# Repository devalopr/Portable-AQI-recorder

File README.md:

# Portable AQI Recorder — V3 (custom PCB)

A handheld air-quality recorder on a custom main board: an ESP32-C3-MINI-1 module reads a Sensirion SEN5x or SEN6x particulate sensor and an optional SCD4x CO₂ sensor (SCD40, SCD41 or SCD43), shows readings on a 2.4" ST7789 TFT with three buttons, and has Wi-Fi and BLE on the module.

This branch holds the **V3 main PCB only**. Everything else lives elsewhere:

| What | Where |
|---|---|
| ESP32-C3 Super Mini build without a PCB: firmware, Web Bluetooth app, wiring | [V2 branch](https://github.com/devalopr/Portable-AQI-recorder/tree/V2) |
| 18650 battery board (IP5310, USB-C in/out, battery % over PWM) | Separate product: [18650-USB-C-UPS](https://github.com/devalopr/18650-USB-C-UPS) (private) |
| Rev A boards and earlier design history | Git history of this branch (commit `34dd5cf`) |

## Main board (Rev B)

**[hardware/rev-b/main](hardware/rev-b/main/README.md)** — KiCad 10 project, 47 × 76 mm, two layers, fully routed. Start with its README: layout, pin map, connectors, cost, checks and open items before fabrication.

- **Display:** 2.4" 240 × 320 ST7789 TFT on the front, with the three buttons below it. An e-paper display can be fitted instead through an external adapter on J6.
- **Sensors:** SEN5x and SEN6x connectors (fit one PM module) and a CO₂ island for an optional SCD40, SCD41 or SCD43, soldered by hand later. Everything else on the board comes assembled; only the CO₂ sensor and the J6/J8 headers are left unfitted.
- **Power and data:** USB-C J1 is the only input. It takes 5 V and USB data from the battery board's USB-C output, or straight from a charger or computer. Battery % arrives as PWM on J2.
- **Cost:** about $4.63 per board at 1000 (parts, 2-layer fabrication and JLC assembly); see [review/COST.md](hardware/rev-b/main/review/COST.md).

## Repository layout

| Path | Contents |
|---|---|
| [firmware](firmware/README.md) | Main board firmware (PlatformIO). |
| [hardware/rev-b/main](hardware/rev-b/main/README.md) | Schematic, PCB, libraries and 3D models; `review/` has the BOM, placement file, PDF, renders, DRC/ERC reports and routing files. |
| [hardware/rev-b/scripts](hardware/rev-b/scripts) | Python/shell pipeline that generates the schematic and places, routes and checks the board (see "Regenerating" in the main README). |
| [hardware/rev-b/firmware/telemetry](hardware/rev-b/firmware/telemetry/README.md) | ESP32 receiver for the battery board's battery-% PWM signal. |
| [hardware/rev-b/references](hardware/rev-b/references) | Datasheets for parts on this board. |
| [hardware/design-brief.md](hardware/design-brief.md) | The original product brief the boards were designed from. |

## Firmware

**[firmware/](firmware/README.md)** — PlatformIO/Arduino firmware for this board, ported from the V2 firmware: auto-detects SEN5x or SEN6x and any SCD4x, shows AQI and the other readings on the TFT, records to RAM, streams over BLE (compatible with the V2 web app) and shows the battery % from the battery board. It builds but hasn't run on a built board yet.

The board is programmed and logs over its USB-C port (the ESP32-C3's native USB): switch the board on and run `pio run -t upload` in `firmware/`. If it stops appearing, hold OK while switching it on to force the bootloader.

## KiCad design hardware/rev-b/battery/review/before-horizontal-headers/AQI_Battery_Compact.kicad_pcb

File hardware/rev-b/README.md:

**Current boards (2026-09-27):** main board [main/](main/README.md) (USB-C input + Dupont battery-PWM header) and the battery board, now its own product in the private [18650-USB-C-UPS](https://github.com/devalopr/18650-USB-C-UPS) repo. The sections below describe earlier battery-board revisions.

# Compact standalone 18650 supply — Rev B engineering review

## Current BOM handoff — 2026-09-11

For continuing cost-reduction work, use [cost-revision/review/engineering-bom.csv](cost-revision/review/engineering-bom.csv) and [the sourcing handoff](cost-revision/BOM-HANDOFF.md). Procurement metadata is synchronized into the cost-revision schematic and design.json. The older battery/review CSV and the routed-board description below describe an earlier circuit.

The generic holder is costed at INR30 based on the user's under-INR30 source. The current priced subset including that allowance is INR261.21 per board at 1,000 boards; unresolved parts and manufacturing remain additional. This is not a complete production quotation.

Open **battery/AQI_Battery_Compact.kicad_pro**. This is the routed electrical revision; the older `AQI_Battery_Compact_Mechanical` file is only the superseded fit study. Rev A is unchanged.

## Size and interfaces

- **26.2 × 88 mm, two copper layers, 1.6 mm board.** Approximately 5.55 mm wider overall than the 20.65 mm holder model. Area is about 42% smaller than the old 44 × 90 mm board.
- Keystone **1042** surface-mount holder for a standard 65 mm cell, with its actual KiCad STEP model. Terminal pad span limits length; the input connector mounting geometry required the extra 0.5 mm over the initial fit study.
- Bottom input: Amphenol **12401610E4#2A**, centred on the board, with surface-mount signal contacts and through-hole shell anchors. Input USB data are passed to the optional GH interface.
- Top output: GCT **USB4135-GF-A**, power-only, all surface mount. TUSB320 attachment detection and TPS2552 switched/current-limited VBUS are included.
- J8/J9: unpopulated 2.54 mm through-hole rows on both sides of the output USB-C, each carrying 3.3 V, 5 V and GND (pins 1–3). Trim soldered wire ends flush on the holder side. Design load targets are 0.5 A at 5 V and 0.3 A at 3.3 V; USB and auxiliary loads share the converter budget. These are not bench-qualified ratings.
- JST GH host connector and MAX17048 fuel gauge retained for AQI compatibility. Neither is required to select charging current or operate the standalone indicator. R18/R19 I2C pullups are intentionally unpopulated when a host supplies pullups.

## Charge-rate selector

Recessed **C&K PCM13SMTR** three-position slide switch. Nominal labels: **500 mA / 1 A / 1.5 A**. Select with input power disconnected. The enclosure should expose a small tool-access opening; the PCB alone cannot enforce tweezers-only access.

BQ25606 switching charger; no MCU, firmware or ESP32 required. VSET is intentionally floating for nominal 4.208 V regulation. R36 (10 kΩ) provides a fixed normal-temperature bypass by default, so no thermistor is required. Optional TH1 is a Vishay NTCS0603E3103FLT 0603 SMD NTC (10 kΩ, B3435). Remove R36 when fitting TH1; never populate both. TH1 measures PCB temperature and does not provide direct cell-temperature monitoring.

R3 = 1.37 kΩ sets the low rate. R4 and R5 = 681 Ω form a tapped resistor ladder selected to ground by switch common pin 3. Calculated nominal rates are approximately **494 / 991 / 1488 mA**. An open selector contact falls back to low; overlapping adjacent contacts cannot add independent parallel branches beyond the high setting. Charger and resistor tolerances still apply.

For a nominal 0.5C target, 1 A corresponds to a 2000 mAh cell and 1.5 A to a 3000 mAh cell. Select within the actual cell manufacturer's charging limit. Cell size does not establish safe charge current. Full charging includes a taper phase and takes longer than two hours at 0.5C.

The input CC controller raises the input limit from nominal 0.50 A to about 1.42 A only when the source advertises at least 1.5 A. Charge current may be reduced by input power, concurrent loads or temperature. Legacy USB host enumeration/current-policy compliance remains a qualification item; this is not a certified universal USB product.

## RGB indicator

One small RGB LED, with 10 kΩ series resistors for dim operation. Autonomous comparator-based battery voltage bands: red below approximately 3.50 V; red + green between approximately 3.50 and 3.91 V; green above approximately 3.91 V. Blue is added during charging and follows the charger fault blink signal. Colours therefore blend while charging. This is an approximate voltage indication, **not a percentage gauge**. The optional MAX17048 supplies percentage data to an external I2C host.

## Validation and limits

- See `battery/review/erc.json`, `drc.json`, `connectivity.json` and `validation.json` for current results.
- All 273 intended electrical pins agree between the schematic netlist and PCB. ERC passes, routing has zero unconnected items and schematic parity passes.
- The dense charger escape includes approximately 2.8 mm total of 0.15 mm battery-net neck-downs; most of the repaired route uses 0.5 mm copper. Verify worst-case charging/discharging temperature rise and voltage drop before production.
- Ten unsuppressed mechanical DRC findings concern opposite-side holder courtyard overlap: four bare-header holes, two input shell anchors, two input locating holes and two selector locating holes. Bare holes are intentionally unpopulated; trim any wires flush. Verify input anchor/peg protrusion and holder clearance with actual parts before fabrication. These findings are not an electrical clearance waiver.
- The STEP includes the actual holder and library component models. RGB, TUSB320 and MAX17048 use explicitly named simplified body/fit models where installed library models were missing. They are not manufacturer-certified detailed CAD.
- Remaining release work: mechanical clearance sign-off, charge/boost thermal and load testing, USB attachment/current-limit behaviour, protection testing, optional temperature-sensing verification, and final exact passive BOM/availability review. Do not order production boards from this engineering package.

## Files

- `battery/AQI_Battery_Compact.kicad_pro`: editable KiCad project.
- `battery/review/AQI_Battery_Compact-fit-check.step`: Fusion fit-check assembly; use Upload/Open in Fusion, then compare to the enclosure.
- `battery/review/compact-holder.png` and `compact-rear.png`: review images.
- `battery/review/engineering-bom.csv`: engineering component list; unresolved passive selections are marked.

The scripts capture intermediate generation and repair operations. The checked-in PCB is the current routed source of truth; do not run the initial generator over it to update a small detail. Back up the working project before regeneration.

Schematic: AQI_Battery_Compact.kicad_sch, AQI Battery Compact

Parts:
C1: 1uF 16V; C_0603_1608Metric
C2: 10uF 16V; C_0805_2012Metric
C3, C4, C17, C19: 22uF 16V; C_0805_2012Metric
C5, C12: 100nF 16V X7R; C_0603_1608Metric; MPN TBD
C6: 4.7uF 10V; C_0603_1608Metric
C7, C11: 10uF 16V X7R; C_0805_2012Metric; MPN TBD
C8, C9, C10, C13, C14: 22uF 16V X7R; C_0805_2012Metric; MPN TBD
C15, C18, C20, C21, C22, C23: 100nF 16V; C_0603_1608Metric
C16: 47nF 16V; C_0603_1608Metric
C24: 100nF 16V X7R; C_0603_1608Metric
D1: Dim RGB; LED_RGB_Lumex_SML-LXT0805SIUGUBW; MPN SML-LXT0805SIUGUBW
D2: USBLC6-2SC6; SOT-23-6; MPN USBLC6-2SC6
J1: USB-C INPUT + DATA; USB_C_Receptacle_Amphenol_12401610E4-2A; MPN 12401610E4#2A
J2: 18650 / Keystone 1042; BatteryHolder_Keystone_1042_BareHeaderClearance; MPN 1042
J3: MAIN BOARD / GH 10; JST_GH_SM10B-GHS-TB_1x10-1MP_P1.25mm_Horizontal; MPN SM10B-GHS-TB
J7: 5V USB-C OUTPUT; USB_C_Receptacle_GCT_USB4135-GF-A_6P_TopMnt_Horizontal; MPN USB4135-GF-A
J8, J9: 3V3 / 5V / GND; PinHeader_1x03_P2.54mm_Vertical; MPN 3V3 / 5V / GND; not fitted
L1: 1uH; L_Coilcraft_XAL5030-XXX; MPN XAL5030-102MEC
L2, L3: 2.2uH; L_Coilcraft_XAL4020-XXX; MPN XAL4020-222MEC
Q2: FS8205A / TSSOP-8; TSSOP-8_4.4x3mm_P0.65mm; MPN FS8205A
Q3: MMBT3904; SOT-23; MPN MMBT3904
Q4: 2N7002; SOT-23; MPN 2N7002
R3: 1.37kR; R_0603_1608Metric
R4, R5: 681R; R_0603_1608Metric
R6: 953R; R_0603_1608Metric
R7: 100kR; R_0603_1608Metric; MPN TBD
R8: 150kR; R_0603_1608Metric; MPN TBD
R9: 470R; R_0603_1608Metric; MPN TBD
R10: 1kR; R_0603_1608Metric; MPN TBD
R11: 523R; R_0603_1608Metric
R12: 5.23kR; R_0603_1608Metric
R13: 750kR 0.1%; R_0603_1608Metric; MPN TBD
R14: 82.5kR 0.1%; R_0603_1608Metric; MPN TBD
R15: 30.9kR; R_0603_1608Metric
R16, R24: 887kR; R_0603_1608Metric
R17, R25, R27, R28, R33, R34, R35: 10kR; R_0603_1608Metric
R18, R19: 4.7kR; R_0603_1608Metric; MPN TBD; not fitted
R20, R21, R23, R30, R32: 100kR; R_0603_1608Metric
R22: 1MR; R_0603_1608Metric
R26: 47.5kR; R_0603_1608Metric
R29: 215kR; R_0603_1608Metric
R31: 182kR; R_0603_1608Metric
R36: 10kR 1%; R_0603_1608Metric
SW1: 500mA / 1A / 1.5A; SW_SP3T_PCM13; MPN PCM13SMTR
TH1: 10kR NTC / 3435K; R_0603_1608Metric; MPN NTCS0603E3103FLT; not fitted
U1: BQ25606 / 4.2V; BQ25606_RGE_ThermalVias_03; MPN BQ25606RGER; LCSC C374063
U2: TPS61023 / 5V; SOT-563; MPN TPS61023DRLR
U3: TPS63031 / 3.3V; WSON-10-1EP_2.5x2.5mm_P0.5mm_EP1.2x2mm; MPN TPS63031DSKR
U4: MAX17048 / 0x36; TDFN-8-1EP_2x2mm_P0.5mm_EP0.8x1.2mm; MPN MAX17048G+T10
U5: DW01A / PROTECTOR; SOT-23-6; MPN DW01A
U6: USB-C INPUT detect; Texas_X2QFN-12_1.6x1.6mm_P0.4mm; MPN TUSB320LAIRWBR
U7: USB-C OUTPUT attach; Texas_X2QFN-12_1.6x1.6mm_P0.4mm; MPN TUSB320LAIRWBR
U8: USB OUT protection; SOT-23-6; MPN TPS2552DBVR
U9: Battery voltage bands; TSSOP-8_3x3mm_P0.65mm; MPN LMV393IPWR
U10: 1.24V reference; SOT-23; MPN TLV431BIDBZR

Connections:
/BOOST_FB: R13.2, R14.1, U2.1 (FB)
/BOOST_L1: L2.1, U3.4 (L1)
/BOOST_L2: L2.2, U3.2 (L2)
/BOOST_SW: L1.2, U2.5 (SW)
/CC_BASE: Q3.1 (B), R20.2
/CC_GATE: Q3.3 (C), Q4.1 (G), R21.2, R22.1
/CELL_NEG: C5.2, J2.2, Q2.2 (S1), Q2.3 (S1), U5.6 (GND)
/CELL_NTC: R12.2, R15.1, R36.1, TH1.1, U1.11 (TS)
/CHARGE_STATUS_N: R35.2, U1.5 (STAT)
/CHG_BTST: C16.1, U1.21 (BTST)
/CHG_ICHG: R3.1, R4.1, U1.10 (ICHG)
/CHG_ILIM: R6.1, R11.1, U1.8 (ILIM)
/CHG_PMID: C2.1, U1.23 (PMID)
/CHG_REGN: C6.1, R12.1, U1.22 (REGN)
/CHG_SW: C16.2, L3.1, U1.19 (SW), U1.20 (SW)
/GREEN_SINK: R34.2, U9.7 (OUT_G)
/I2C_SCL: J3.8, R19.1, U4.7 (SCL)
/I2C_SDA: J3.7, R18.1, U4.8 (SDA)
/ILIM_BRANCH: Q4.3 (D), R11.2
/INPUT_HIGH_N: R17.2, R20.1, U6.7 (OUT1)
/INPUT_VDET: R16.2, U6.4 (VBUS_DET)
/LED_BLUE: D1.1 (B_K), R35.1
/LED_GREEN: D1.4 (G_K), R34.1
/LED_RED: D1.3 (R_K), R33.1
/OUTPUT_VDET: R24.2, U7.4 (VBUS_DET)
/OUT_ATTACH_N: R25.2, U7.9 (ID_N), U8.3 (EN_N)
/OUT_CC1: J7.A5 (CC1), U7.1 (CC1)
/OUT_CC2: J7.B5 (CC2), U7.2 (CC2)
/OUT_ILIM: R26.1, U8.5 (ILIM)
/PROT_CENTER: Q2.1 (D12), Q2.8 (D12)
/PROT_CS: R10.1, U5.2 (CS)
/PROT_OC: Q2.5 (G2), U5.3 (OC)
/PROT_OD: Q2.4 (G1), U5.1 (OD)
/PROT_VCC: C5.1, R9.2, U5.5 (VCC)
/RATE_HIGH: R4.2, R5.1, SW1.4 (HIGH)
/RATE_MED: R5.2, SW1.2 (MED)
/RED_SINK: R33.2, U9.1 (OUT_R)
/SOURCE_MODE: R23.2, U7.3 (PORT)
/USB_CC1: J1.A5, U6.1 (CC1)
/USB_CC2: J1.B5, U6.2 (CC2)
/USB_D+: D2.1 (I/O1), D2.6 (I/O1), J1.A6, J1.B6, J3.5
/USB_D-: D2.3 (I/O2), D2.4 (I/O2), J1.A7, J1.B7, J3.4
/USB_HOST_PRESENT: J3.10, R7.2, R8.1
/USB_VBUS_IN: C1.1, C15.1, D2.5 (VBUS), J1.A4, J1.A9, J1.B4, J1.B9, R7.1, R16.1, R17.1, R21.1, U1.1 (VAC), U1.24 (VBUS), U6.12 (VDD)
/USB_VBUS_OUT: C19.1, J7.A9 (VBUS), J7.B9 (VBUS), R24.1, R27.1, U8.6 (OUT)
/VBAT_HIGH_DIV: C22.1, R29.2, R30.1, U9.3 (IN_R+)
/VBAT_LOW_DIV: C23.1, R31.2, R32.1, U9.6 (IN_G-)
/VREF_1V24: R28.2, U9.2 (IN_R-), U9.5 (IN_G+), U10.1 (REF), U10.2 (K)
BOOST_5V: C8.1, C9.1, C10.1, C20.1, D1.2 (A), J3.1, J3.2, J8.2, J9.2, R13.1, U2.6 (VOUT), U8.1 (IN)
CELL_POS: C4.1, C24.1, J2.1, R9.1, R29.1, R31.1, U1.13 (BAT), U1.14 (BAT), U4.2 (CELL), U4.3 (VDD)
CHG_SYS: C3.1, C7.1, C11.1, C12.1, C17.1, L1.1, L3.2, U1.15 (SYS), U1.16 (SYS), U2.2 (EN), U2.3 (VIN), U3.5 (VIN), U3.6 (EN), U3.8 (VINA)
GEN_3V3: C13.1, C14.1, C18.1, C21.1, J8.1, J9.1, R18.2, R19.2, R23.1, R25.1, R28.1, U3.1 (VOUT), U3.10 (FB), U7.12 (VDD), U9.8 (VCC)
GND: C1.2, C2.2, C3.2, C4.2, C6.2, C7.2, C8.2, C9.2, C10.2, C11.2, C12.2, C13.2, C14.2, C15.2, C17.2, C18.2, C19.2, C20.2, C21.2, C22.2, C23.2, C24.2, D2.2 (GND), J1.A1, J1.A12, J1.B1, J1.B12, J1.SH (SHIELD), J3.3, J3.6, J3.9, J7.A12 (GND), J7.B12 (GND), J7.SH (SHIELD), J8.3, J9.3, Q2.6 (S2), Q2.7 (S2), Q3.2 (E), Q4.2 (S), R3.2, R6.2, R8.2, R10.2, R14.2, R15.2, R22.2, R26.2, R27.2, R30.2, R32.2, R36.2, SW1.3 (COMMON), TH1.2, U1.6 (OTG), U1.9 (CE_N), U1.17 (GND), U1.18 (GND), U1.25 (EP), U2.4 (GND), U3.3 (PGND), U3.7 (PS/SYNC), U3.9 (GND), U3.11 (PGND), U4.1 (CTG), U4.4 (GND), U4.6 (QSTRT), U4.9 (EP), U6.3 (PORT), U6.10 (GND), U6.11 (EN_N), U7.10 (GND), U7.11 (EN_N), U8.2 (GND), U9.4 (GND), U10.3 (A)

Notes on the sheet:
USB INPUT / source detection
CHARGER / optional PCB temperature sensing
CHARGE RATE / recessed selector
CELL / independent protection
5V CONVERTER / shared 0.5A target
3.3V CONVERTER / 0.3A target
USB OUTPUT / attach and current limit
STANDALONE RGB / voltage estimate
OPTIONAL HOST / fuel gauge and USB
COMPACT 18650 POWER / REV B ENGINEERING
2 layers / 26.2 x 88mm. 4.2V Li-ion only. 500mA / 1A / 1.5A nominal. No host or firmware required.

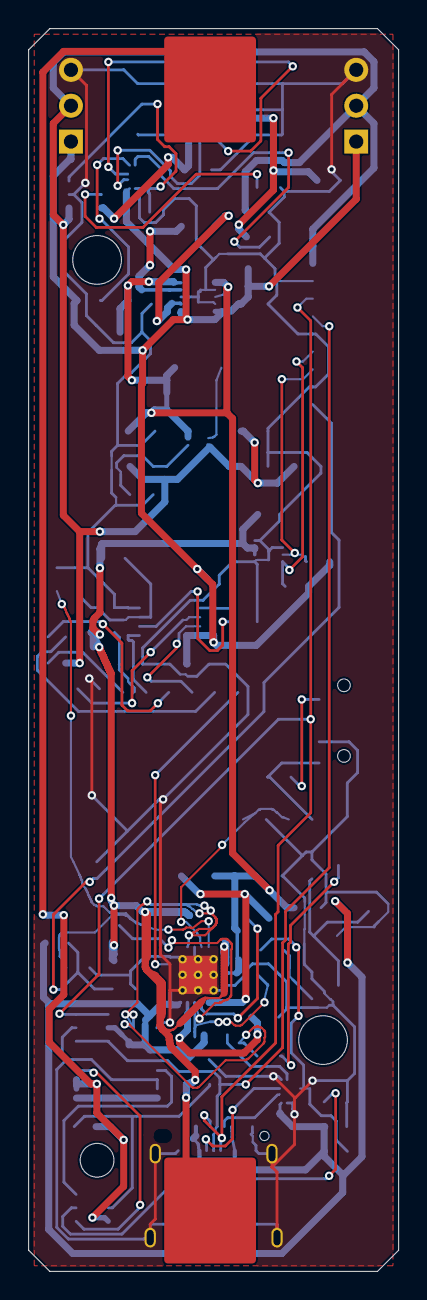
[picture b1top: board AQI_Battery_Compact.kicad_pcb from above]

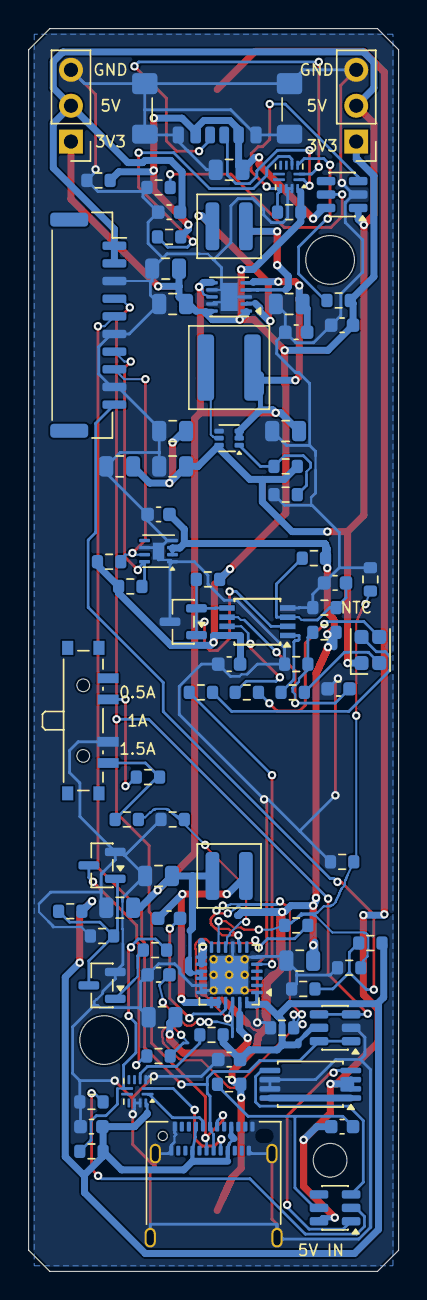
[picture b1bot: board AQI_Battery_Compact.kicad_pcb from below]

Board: 2 copper layers, 26.2 x 88.0 mm, 84 parts (83 on the bottom side), 53 nets.

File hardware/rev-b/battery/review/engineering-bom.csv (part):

Reference,Value,MPN,Manufacturer,Footprint,DNP,Note
J1,USB-C INPUT + DATA,12401610E4#2A,Amphenol,Connector_USB:USB_C_Receptacle_Amphenol_12401610E4-2A,False,USB2 data retained. Unused SuperSpeed and SBU contacts NC. Matching library STEP model; centred on 26.2mm board.
J2,18650 / Keystone 1042,1042,Keystone,AQI:BatteryHolder_Keystone_1042_BareHeaderClearance,False,Stock Keystone 1042 pad geometry; silk moved to fabrication layer to clear auxiliary holes. Actual holder STEP retained.
J3,MAIN BOARD / GH 10,SM10B-GHS-TB,JST,Connector_JST:JST_GH_SM10B-GHS-TB_1x10-1MP_P1.25mm_Horizontal,False,Optional AQI link. Standalone charging and outputs do not require this connector.
U2,TPS61023 / 5V,TPS61023DRLR,Texas Instruments,Package_TO_SOT_SMD:SOT-563,False,
U3,TPS63031 / 3.3V,TPS63031DSKR,Texas Instruments,Package_SON:WSON-10-1EP_2.5x2.5mm_P0.5mm_EP1.2x2mm,False,
U4,MAX17048 / 0x36,MAX17048G+T10,Analog Devices,Package_DFN_QFN:TDFN-8-1EP_2x2mm_P0.5mm_EP0.8x1.2mm,False,Optional I2C fuel gauge for host; no host needed for charging or indicator.
U5,DW01A / PROTECTOR,DW01A,Tani,Package_TO_SOT_SMD:SOT-23-6,False,Exact Tani thresholds; never substitute without checking voltage thresholds and delay times.
Q2,FS8205A / TSSOP-8,FS8205A,Fortune Semiconductor,Package_SO:TSSOP-8_4.4x3mm_P0.65mm,False,
L1,1uH,XAL5030-102MEC,Coilcraft,Inductor_SMD:L_Coilcraft_XAL5030-XXX,False,
L2,2.2uH,XAL4020-222MEC,Coilcraft,Inductor_SMD:L_Coilcraft_XAL4020-XXX,False,
R7,100kR,TBD,TBD,Resistor_SMD:R_0603_1608Metric,False,
R8,150kR,TBD,TBD,Resistor_SMD:R_0603_1608Metric,False,
R9,470R,TBD,TBD,Resistor_SMD:R_0603_1608Metric,False,
R10,1kR,TBD,TBD,Resistor_SMD:R_0603_1608Metric,False,
C5,100nF 16V X7R,TBD,TBD,Capacitor_SMD:C_0603_1608Metric,False,
R13,750kR 0.1%,TBD,TBD,Resistor_SMD:R_0603_1608Metric,False,
R14,82.5kR 0.1%,TBD,TBD,Resistor_SMD:R_0603_1608Metric,False,
C7,10uF 16V X7R,TBD,TBD,Capacitor_SMD:C_0805_2012Metric,False,
C8,22uF 16V X7R,TBD,TBD,Capacitor_SMD:C_0805_2012Metric,False,
C9,22uF 16V X7R,TBD,TBD,Capacitor_SMD:C_0805_2012Metric,False,
C10,22uF 16V X7R,TBD,TBD,Capacitor_SMD:C_0805_2012Metric,False,
C11,10uF 16V X7R,TBD,TBD,Capacitor_SMD:C_0805_2012Metric,False,
C12,100nF 16V X7R,TBD,TBD,Capacitor_SMD:C_0603_1608Metric,False,
C13,22uF 16V X7R,TBD,TBD,Capacitor_SMD:C_0805_2012Metric,False,
C14,22uF 16V X7R,TBD,TBD,Capacitor_SMD:C_0805_2012Metric,False,
R18,4.7kR,TBD,TBD,Resistor_SMD:R_0603_1608Metric,True,Populate only for independent I2C operation. Main PCB supplies the pullups.
R19,4.7kR,TBD,TBD,Resistor_SMD:R_0603_1608Metric,True,Populate only for independent I2C operation. Main PCB supplies the pullups.
D2,USBLC6-2SC6,USBLC6-2SC6,STMicroelectronics,Package_TO_SOT_SMD:SOT-23-6,False,
U1,BQ25606 / 4.2V,BQ25606RGER,Texas Instruments,AQI:BQ25606_RGE_ThermalVias_03,False,VSET must FLOAT for 4.2V. D+/D- float so ILIM controls unknown-adapter input limit; GH USB data remain separate. R36 supplies the normal-temperature bypass by default. Remove R36 when fitting TH1.
L3,2.2uH,XAL4020-222MEC,Coilcraft,Inductor_SMD:L_Coilcraft_XAL4020-XXX,False,
C1,1uF 16V,SELECT EXACT PART,,Capacitor_SMD:C_0603_1608Metric,False,X7R; verify effective capacitance at operating bias
C2,10uF 16V,SELECT EXACT PART,,Capacitor_SMD:C_0805_2012Metric,False,X7R; verify effective capacitance at operating bias
C3,22uF 16V,SELECT EXACT PART,,Capacitor_SMD:C_0805_2012Metric,False,X7R; verify effective capacitance at operating bias
C4,22uF 16V,SELECT EXACT PART,,Capacitor_SMD:C_0805_2012Metric,False,X7R; verify effective capacitance at operating bias
C6,4.7uF 10V,SELECT EXACT PART,,Capacitor_SMD:C_0603_1608Metric,False,X7R; verify effective capacitance at operating bias
C16,47nF 16V,SELECT EXACT PART,,Capacitor_SMD:C_0603_1608Metric,False,X7R; verify effective capacitance at operating bias
C17,22uF 16V,SELECT EXACT PART,,Capacitor_SMD:C_0805_2012Metric,False,X7R; verify effective capacitance at operating bias
R3,1.37kR,SELECT EXACT PART,,Resistor_SMD:R_0603_1608Metric,False,1% unless explicitly stated
R4,681R,SELECT EXACT PART,,Resistor_SMD:R_0603_1608Metric,False,1% unless explicitly stated
R5,681R,SELECT EXACT PART,,Resistor_SMD:R_0603_1608Metric,False,1% unless explicitly stated
SW1,500mA / 1A / 1.5A,PCM13SMTR,C&K,Button_Switch_SMD:SW_SP3T_PCM13,False,Recessed actuator. Pin3 common. Ladder limits overlapping contacts to HIGH; open contact falls back LOW. Adjust with input power disconnected.
R6,953R,SELECT EXACT PART,,Resistor_SMD:R_0603_1608Metric,False,1% unless explicitly stated
R11,523R,SELECT EXACT PART,,Resistor_SMD:R_0603_1608Metric,False,1% unless explicitly stated
R12,5.23kR,SELECT EXACT PART,,Resistor_SMD:R_0603_1608Metric,False,1% unless explicitly stated
R15,30.9kR,SELECT EXACT PART,,Resistor_SMD:R_0603_1608Metric,False,1% unless explicitly stated
U6,USB-C INPUT detect,TUSB320LAIRWBR,Texas Instruments,Package_DFN_QFN:Texas_X2QFN-12_1.6x1.6mm_P0.4mm,False,
R16,887kR,SELECT EXACT PART,,Resistor_SMD:R_0603_1608Metric,False,1% unless explicitly stated
R17,10kR,SELECT EXACT PART,,Resistor_SMD:R_0603_1608Metric,False,1% unless explicitly stated
C15,100nF 16V,SELECT EXACT PART,,Capacitor_SMD:C_0603_1608Metric,False,X7R; verify effective capacitance at operating bias
Q3,MMBT3904,MMBT3904,onsemi,Package_TO_SOT_SMD:SOT-23,False,
R20,100kR,SELECT EXACT PART,,Resistor_SMD:R_0603_1608Metric,False,1% unless explicitly stated
R21,100kR,SELECT EXACT PART,,Resistor_SMD:R_0603_1608Metric,False,1% unless explicitly stated
R22,1MR,SELECT EXACT PART,,Resistor_SMD:R_0603_1608Metric,False,1% unless explicitly stated
Q4,2N7002,2N7002,Nexperia,Package_TO_SOT_SMD:SOT-23,False,
J7,5V USB-C OUTPUT,USB4135-GF-A,GCT,Connector_USB:USB_C_Receptacle_GCT_USB4135-GF-A_6P_TopMnt_Horizontal,False,
U7,USB-C OUTPUT attach,TUSB320LAIRWBR,Texas Instruments,Package_DFN_QFN:Texas_X2QFN-12_1.6x1.6mm_P0.4mm,False,
R23,100kR,SELECT EXACT PART,,Resistor_SMD:R_0603_1608Metric,False,1% unless explicitly stated
R24,887kR,SELECT EXACT PART,,Resistor_SMD:R_0603_1608Metric,False,1% unless explicitly stated
R25,10kR,SELECT EXACT PART,,Resistor_SMD:R_0603_1608Metric,False,1% unless explicitly stated
C18,100nF 16V,SELECT EXACT PART,,Capacitor_SMD:C_0603_1608Metric,False,X7R; verify effective capacitance at operating bias
U8,USB OUT protection,TPS2552DBVR,Texas Instruments,Package_TO_SOT_SMD:SOT-23-6,False,
R26,47.5kR,SELECT EXACT PART,,Resistor_SMD:R_0603_1608Metric,False,1% unless explicitly stated
R27,10kR,SELECT EXACT PART,,Resistor_SMD:R_0603_1608Metric,False,1% unless explicitly stated
C19,22uF 16V,SELECT EXACT PART,,Capacitor_SMD:C_0805_2012Metric,False,X7R; verify effective capacitance at operating bias
C20,100nF 16V,SELECT EXACT PART,,Capacitor_SMD:C_0603_1608Metric,False,X7R; verify effective capacitance at operating bias
U9,Battery voltage bands,LMV393IPWR,Texas Instruments,Package_SO:TSSOP-8_3x3mm_P0.65mm,False,
U10,1.24V reference,TLV431BIDBZR,Texas Instruments,Package_TO_SOT_SMD:SOT-23,False,
R28,10kR,SELECT EXACT PART,,Resistor_SMD:R_0603_1608Metric,False,1% unless explicitly stated
R29,215kR,SELECT EXACT PART,,Resistor_SMD:R_0603_1608Metric,False,1% unless explicitly stated
R30,100kR,SELECT EXACT PART,,Resistor_SMD:R_0603_1608Metric,False,1% unless explicitly stated
R31,182kR,SELECT EXACT PART,,Resistor_SMD:R_0603_1608Metric,False,1% unless explicitly stated
R32,100kR,SELECT EXACT PART,,Resistor_SMD:R_0603_1608Metric,False,1% unless explicitly stated
C21,100nF 16V,SELECT EXACT PART,,Capacitor_SMD:C_0603_1608Metric,False,X7R; verify effective capacitance at operating bias
C22,100nF 16V,SELECT EXACT PART,,Capacitor_SMD:C_0603_1608Metric,False,X7R; verify effective capacitance at operating bias
C23,100nF 16V,SELECT EXACT PART,,Capacitor_SMD:C_0603_1608Metric,False,X7R; verify effective capacitance at operating bias
D1,Dim RGB,SML-LXT0805SIUGUBW,Lumex,LED_SMD:LED_RGB_Lumex_SML-LXT0805SIUGUBW,False,
R33,10kR,SELECT EXACT PART,,Resistor_SMD:R_0603_1608Metric,False,1% unless explicitly stated
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
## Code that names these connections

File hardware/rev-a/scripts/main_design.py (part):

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# custom import path specified for generator; pin contract uses official symbol.
pn={str(i):None for i in range(1,54)}
for n in [1,2,11,14,36,37,38,39,40,41,42,43,44,45,46,47,48,49,50,51,52,53]:pn[str(n)]='GND'
pn.update({str(k):v for k,v in {3:'+3V2',5:'BOOT_GPIO2',6:'BL_PWM',8:'MCU_EN',12:'I2C_SDA',13:'I2C_SCL',16:'DISP_CS',18:'DISP_SCK',19:'DISP_DC',20:'DISP_MOSI',21:'DISP_RST',22:'BOOT_GPIO8',23:'BOOT_GPIO9',26:'USB_MCU_D-',27:'USB_MCU_D+',30:'EPD_BUSY',31:'UART_TX'}.items()})
add('U1','AQI:ESP32-C3-MINI-1-H4','ESP32-C3-MINI-1-H4',pn,(74,80),(35,68),'AQI:ESP32-C3-MINI-1',rot=180,mpn='ESP32-C3-MINI-1-H4',manufacturer='Espressif',datasheet='https://documentation.espressif.com/esp32-c3-mini-1_datasheet_en.html')
r(1,'10kR','+3V2','MCU_EN',(137,45),(26,69));c(1,'1uF 16V','MCU_EN','GND',(163,45),(26,71));c(2,'10uF 25V','+3V2','GND',(137,75),(26,73),C8);c(3,'100nF 25V','+3V2','GND',(163,75),(26,75))
r(2,'10kR','+3V2','BOOT_GPIO9',(137,105),(27,65));r(3,'10kR','+3V2','BOOT_GPIO8',(163,105),(29,65));r(4,'10kR','+3V2','BOOT_GPIO2',(137,133),(31,65))
# service pads, boot and reset can be shorted to nearby ground during recovery.
for i,(net,x,y) in enumerate([('GND',4,74),('MCU_EN',7,74),('BOOT_GPIO9',10,74),('UART_TX',13,74),('EPD_BUSY',16,74),('+3V2',19,74)],1):
 add('TP'+str(i),'Connector:TestPoint',net,{1:net},(23+(i-1)*28,152),(x,y),'TestPoint:TestPoint_Pad_D1.0mm')
# Local USB and combined GH input
un={p:'GND' for p in ['A1','A12','B1','B12','SH']};un.update({p:'+5V_USB' for p in ['A4','A9','B4','B9']});un.update({'A5':'USB_CC1','B5':'USB_CC2','A6':'USB_LOCAL_D+','B6':'USB_LOCAL_D+','A7':'USB_LOCAL_D-','B7':'USB_LOCAL_D-','A8':None,'B8':None})
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
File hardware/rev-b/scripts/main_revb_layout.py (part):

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    ripup(b, {'+3V3_CO2'}, box=(19.3, 65.0, 19.7, 66.0), layers=('B',))
    ripup(b, {'GND'}, box=(17.5, 62.5, 19.6, 64.6), layers=('B',))
    # Buttons, strap nets, backlight, bucks and power switch are rerouted for the new parts.
    ripup(b, {'/BOOT_GPIO2', '/BOOT_GPIO8', '/BOOT_GPIO9', '/MCU_EN'}, box=(15.5, 20, 44, 70))
    ripup(b, {'/BOOT_GPIO2'})
    ripup(b, {'/BOOT_GPIO8'}, box=(12.5, 20, 40, 62.5))
    ripup(b, {'/CORE_SW', '/PM_SW', '/CORE_FB', '/PM_FB'})
    ripup(b, {'+5V_SW', 'GND', '+3V2'}, box=(3.0, 45.5, 13.5, 50.5), layers=('B',))
    ripup(b, {'+5V_SW', 'GND', '+3V3_PM'}, box=(1.0, 20.5, 11.5, 25.5), layers=('B',))
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    track(b, '+5V_SYS', 'B', [(15.74, 56.84), (15.74, 57.34)], 0.3)
    track(b, '+5V_SYS', 'B', [(14.26, 56.84), (14.26, 57.84)], 0.3)
    # C42 up against U7 (output fed between its pins); C3 (100 nF) beside the ESP32 3V3 pin, C2 (10 uF)
    # in C3's old spot; GPIO8 strap pull-up next to the module.
    move(b, 'C42', 21.46, 64.25, 0)
    track(b, '+3V3_CO2', 'B', [(19.86, 61.14), (20.98, 62.25), (20.98, 64.25)], 0.3)
    fp = {f.GetReference(): f for f in b.GetFootprints()}
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    fp['C2'].SetPosition(p3); fp['C3'].SetPosition(p2)
    ripup(b, {'GND'}, box=(9.9, 59.6, 13.0, 62.6), layers=('B',))
    orient(b, 'R3', 11.6, 61.0, first_pad_up=True)
    track(b, '/BOOT_GPIO8', 'B', [(12.2, 62.75), (11.6, 62.15), (11.6, 61.8)])
    track(b, '+3V2', 'B', [(11.6, 60.2), (9.22, 60.2), (8.82, 60.0)], 0.3)


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    track(b, '/USB_MCU_D-', 'B', [(18.1, 71.1), (18.1, 65.3), (14.9, 65.3)])
    track(b, '/USB_D+', 'B', [(18.06, 78.0), (16.9, 78.0), (16.9, 69.7)])
    track(b, '/USB_MCU_D+', 'B', [(16.9, 68.1), (16.9, 66.1), (14.9, 66.1)])
    # Battery PWM: GPIO21 -> via -> inner layer north of VBUS -> via -> R34 / TP4 by J2; R33 pull-up.
    j2 = place_header(b, 'J2', 33.85, 75.35)             # pin 1 GND, pin 2 BAT_PWM
    j8 = place_header(b, 'J8', 39.95, 75.35)             # pin 1 GND, pin 2 EXT_5V
    xm = (j2['1'][0] + j2['2'][0]) / 2
    track(b, '/BAT_PWM_MCU', 'B', [(14.9, 69.3), (15.95, 69.3)]); via(b, '/BAT_PWM_MCU', 15.95, 69.3)
    track(b, '/BAT_PWM_MCU', 'In2', [(15.95, 69.3), (16.65, 70.0), (33.8, 70.0)])
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

def buttons(b):
    """Front buttons on a 13 mm pitch, symmetric about the board centre: LEFT (x 9) -> GPIO8, OK (x 22) ->
    GPIO9 / BOOT, RIGHT (x 35) -> GPIO2."""
    for ref, x in [('SW1', 9.0), ('SW2', 22.0), ('SW3', 35.0)]:
        move(b, ref, x, 66.25)
    # LEFT / GPIO8: right-hand pad 1 drops onto the pin-22 escape via.
    track(b, '/BOOT_GPIO8', 'F', [(12.0, 64.375), (12.2, 63.9), (12.2, 62.75)])
    track(b, '/BOOT_GPIO8', 'F', [(6.0, 64.375), (6.8, 65.2), (11.2, 65.2), (12.0, 64.375)])
    # OK / GPIO9: the MAIN_QOD via under its right pad moves along its inner track; a spare GND via goes.
    ripup(b, {'/MAIN_QOD'}, box=(24.2, 64.2, 25.3, 65.3), layers=('B', 'In2', 'via'))
    track(b, '/MAIN_QOD', 'In2', [(19.31, 59.6), (19.31, 59.75), (23.4, 63.84), (23.85, 64.29), (23.85, 65.5)])
    # +5V_SW from U7 hugs x 23 so the via fits beside R16 pad 2.
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                             (24.82, 66.58)], 0.5)
    via(b, '/MAIN_QOD', 23.85, 65.5)
    track(b, '/MAIN_QOD', 'B', [(23.85, 65.5), (24.675, 65.5)])
    track(b, '/BOOT_GPIO9', 'F', [(19.0, 64.375), (20.0, 65.375), (20.0, 66.6), (24.7, 66.6), (24.7, 65.2),
                                  (25.0, 64.9), (25.0, 64.375)])
    track(b, '/BOOT_GPIO9', 'F', [(19.0, 64.375), (18.2, 63.55), (17.3, 63.5)]); via(b, '/BOOT_GPIO9', 17.3, 63.5)
    track(b, '/BOOT_GPIO9', 'In2', [(17.3, 63.5), (13.4, 63.5), (13.0, 64.45)])
    # RIGHT / GPIO2: pin-5 escape via, front run under the buttons, pull-up R4 behind SW3.
    track(b, '/BOOT_GPIO2', 'B', [(3.1, 69.3), (2.25, 69.25)]); via(b, '/BOOT_GPIO2', 2.25, 69.25)
    track(b, '/BOOT_GPIO2', 'F', [(2.25, 69.25), (2.9, 69.9), (22.5, 69.9), (23.5, 68.9), (29.6, 68.9), (30.95, 67.55),
                                  (30.95, 65.45), (32.0, 64.375)])
    track(b, '/BOOT_GPIO2', 'F', [(32.0, 64.375), (32.8, 63.55), (37.2, 63.55), (38.0, 64.375)])
    # MAIN_ON's via sat under SW3's right pad: drop it between the pads instead.
    ripup(b, {'/MAIN_ON'}, box=(37.0, 64.0, 37.8, 64.7))
    track(b, '/MAIN_ON', 'In2', [(35.2, 62.13), (36.6, 63.53), (36.6, 65.0)]); via(b, '/MAIN_ON', 36.6, 65.0)
    track(b, '/MAIN_ON', 'B', [(36.6, 65.0), (37.55, 65.95), (38.9, 65.95)])
    orient_to(b, 'R4', 32.0, 63.0, {'1': (-1, 0), '2': (1, 0)})
    track(b, '+3V2', 'B', [(31.175, 63.0), (30.82, 64.56)], 0.3)
    track(b, '/BOOT_GPIO2', 'B', [(32.825, 63.0), (33.6, 63.0)]); via(b, '/BOOT_GPIO2', 33.6, 63.0)
    track(b, '/BOOT_GPIO2', 'F', [(33.6, 63.0), (33.2, 63.55)])


def models(b):
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
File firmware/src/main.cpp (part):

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 * - Three buttons: LEFT/RIGHT move the selection, OK opens/closes a chart,
 *   holding OK starts/stops recording. OK on the gear cycles the backlight brightness.
 * - Streams samples over BLE (same service as V2, so the V2 web app works).
 * - Reads battery % from the battery board (PWM on J2 -> GPIO21).
 * - Logs over native USB (the same USB-C port used for programming).
 */

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//  Board pins (main board Rev B; see hardware/rev-b/main/README.md)
// ---------------------------------------------------------------------------

static constexpr uint8_t PIN_I2C_SDA = 0;
static constexpr uint8_t PIN_I2C_SCL = 1;
static constexpr uint8_t PIN_BAT_PWM = 21;   // through R34; R33 pull-up. Never start UART0 TX here.
// Display (DC 10, CS 4, SCK 5, MOSI 6, RST 7) is set in platformio.ini; backlight GPIO3 in display.cpp.
// GPIO20 is the e-paper BUSY input on J6 (e-paper builds only; not used by this TFT firmware).

// ---------------------------------------------------------------------------
//  State
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  prefs.begin("aqi", false);
  setBrightnessIndex(prefs.getUChar("bright", 0));

  BatteryPwmReader::begin(PIN_BAT_PWM);

  // ~64 KB of history: 2700 samples x 24 bytes = 45 min at 1 Hz.
  if (!dataBuffer.begin(2700)) Serial.println("ERROR: data buffer allocation failed.");

  Wire.begin(PIN_I2C_SDA, PIN_I2C_SCL, 100000);
  sensors_begin(Wire);
  setupWebBleService();

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
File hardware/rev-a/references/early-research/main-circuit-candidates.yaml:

version: 1
status: schematic-input-only
sources:
  tps2116: https://www.ti.com/lit/gpn/TPS2116
  ts3usb30e: https://www.ti.com/lit/ds/symlink/ts3usb30e.pdf
  tps62160: https://www.ti.com/lit/ds/symlink/tps62160.pdf
  tps7a20: https://www.ti.com/lit/ds/symlink/tps7a20.pdf
  stcs05a: https://www.st.com/resource/en/datasheet/stcs05a.pdf
  mcp23008: https://ww1.microchip.com/downloads/aemDocuments/documents/APID/ProductDocuments/DataSheets/MCP23008-and-MCP23S08-Data-Sheet-DS20001919.pdf
  esp32_c3_mini_1: https://documentation.espressif.com/esp32-c3-mini-1_datasheet_en.html
components:
  U_PWR1:
    mpn: TPS2116DRLR
    symbol: Power_Management:TPS2116DRL
    footprint: Package_TO_SOT_SMD:SOT-583-8
    pins: {1: GND, 2: SYS_5V, 3: USB5V_LOCAL, 4: USB5V_LOCAL, 5: USB5V_LOCAL, 6: USB5V_INTERNAL, 7: SYS_5V, 8: PWR_MUX_ST}
  U_USB1:
    mpn: TS3USB30EDGSR
    symbol: Interface_USB:TS3USB30EDGSR
    footprint: Package_SO:TSSOP-10_3x3mm_P0.5mm
    pins: {1: USB_SEL_INTERNAL, 2: USB_DP_LOCAL, 3: USB_DP_INTERNAL, 4: USB_DP_MCU, 5: GND, 6: USB_DM_MCU, 7: USB_DM_INTERNAL, 8: USB_DM_LOCAL, 9: USB_MUX_OE_N, 10: 3V3}
  U_CORE1:
    mpn: TPS62160DGKR
    symbol: Regulator_Switching:TPS62160DGK
    footprint: Package_SO:VSSOP-8_3.0x3.0mm_P0.65mm
    pins: {1: GND, 2: SYS_5V, 3: MAIN_RAIL_EN, 4: GND, 5: CORE_FB, 6: 3V3, 7: CORE_SW, 8: CORE_PGOOD}
  U_SCDLDO1:
    mpn: TPS7A2033PDBVR
    symbol: project_local:TPS7A2033PDBVR
    footprint: Package_TO_SOT_SMD:SOT-23-5
    pins: {1: 3V3, 2: GND, 3: SCD_RAIL_EN, 4: NC, 5: SCD_3V3}
  U_BL1:
    mpn: STCS05ADR
    symbol: project_local:STCS05ADR
    footprint: Package_SO:SOIC-8_3.9x4.9mm_P1.27mm
    nets: {VCC: SYS_5V, DRAIN: LCD_BL_K, PWM: LCD_BL_PWM, EN: MAIN_RAIL_EN, FB: BL_FB, GND: GND}
  U_IO1:
    mpn: MCP23008-xSO
    symbol: Interface_Expansion:MCP23008-xSO
    footprint: Package_SO:SOIC-18_3.9x9.9mm_P1.27mm
    pins: {1: I2C_SCL, 2: I2C_SDA, 3: GND, 4: GND, 5: GND, 6: MCU_EN, 7: NC, 8: NC, 9: GND, 10: BTN_UP_N, 11: BTN_DOWN_N, 12: BTN_SELECT_N, 13: IO_SPARE3, 14: IO_SPARE4, 15: IO_SPARE5, 16: IO_SPARE6, 17: IO_SPARE7, 18: 3V3}
  U_MCU1:
    mpn: ESP32-C3-MINI-1-H4X
    symbol: project_local:ESP32-C3-MINI-1-H4X
    footprint: project_local:ESP32-C3-MINI-1
    pads: {3: 3V3, 8: MCU_EN, 12: I2C_SDA, 13: I2C_SCL, 16: LCD_CS, 18: LCD_SCLK, 19: LCD_DC, 20: LCD_MOSI, 21: LCD_RESET, 26: USB_DM_MCU, 27: USB_DP_MCU, 30: EPAPER_BUSY, 31: SERVICE_TX}
logic:
  usb_sel_internal: "INT_HOST_PRESENT AND NOT LOCAL_VBUS_PRESENT"
  usb_mux_truth:
    '0': USB_LOCAL
    '1': USB_INTERNAL
  tps2116_mode: priority
